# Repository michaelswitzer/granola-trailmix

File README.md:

# TrailMix by Granola Arcade

The TrailMix is a button box style arcade controller by Granola Arcade. It is designed to provide the minimum cost professional grade arcade stick available. The design of the TrailMix is simplified down to the core, without any of the bells and whistles that add cost and complexity. Win your local without breaking the bank!

You can no longer buy the TrailMix from Granola but you can buy our current controllers at https://granola.games

## Should you make a TrailMix?
Building your own TrailMix will definitely be more expensive than buying one directly from Granola Arcade, and it isn't as fun to put together as some of the other DIY options out there. Nevertheless, if you decide to press on, the files in this repository should have everything you need.

## How to build
To build your own TrailMix, import the PCB designs and bill of materials using KiCAD. I provided a list of parts that use JLCPCB's part assembly services, since that is the company I use to manufacture the PCB. You can use these files as a starting point for building your own PCB.

The STL file for the case is optimized for FDM 3D printers. I recommend PLA with at least 15% infill but you can use any material you wish. The case is designed to be printed on the thin edge on the top side, which can cause some stability challenges when printing. **This orientation is better suited to printers that do not move their print bed side to side, and can be tricky to print on Prusa/Ender/etc. printers.** If you use a "bed slinger" printer such as these, make sure you have good bed adhesion.

You will also need to source your own key switches and keycaps. The TrailMix uses Kailh low-profile "Choc v1" keyboard switches.

## Firmware
The TrailMix is designed to use the <a rel="GP2040-CE firmware" href="https://github.com/OpenStickCommunity/GP2040-CE">GP2040-CE firmware</a>. You want the .uf2 file for the Raspberry Pi Pico as it has the same pinouts as the TrailMix. If you wish to use different firmware, you can view the schematic files to understand the layout of the board. If you bridge the Boot and GND pins (marked "BOOT" on the PCB) as you plug in the USB cord, you can upload new firmware in .uf2 format.

## Credits
The TrailMix was designed by Michael Switzer. The GP2040-CE firmware is maintained by <a href="https://github.com/OpenStickCommunity">OpenStickCommunity</a>. This project was inspired by the <a href="https://github.com/jfedor2/flatbox">Flatbox</a>.

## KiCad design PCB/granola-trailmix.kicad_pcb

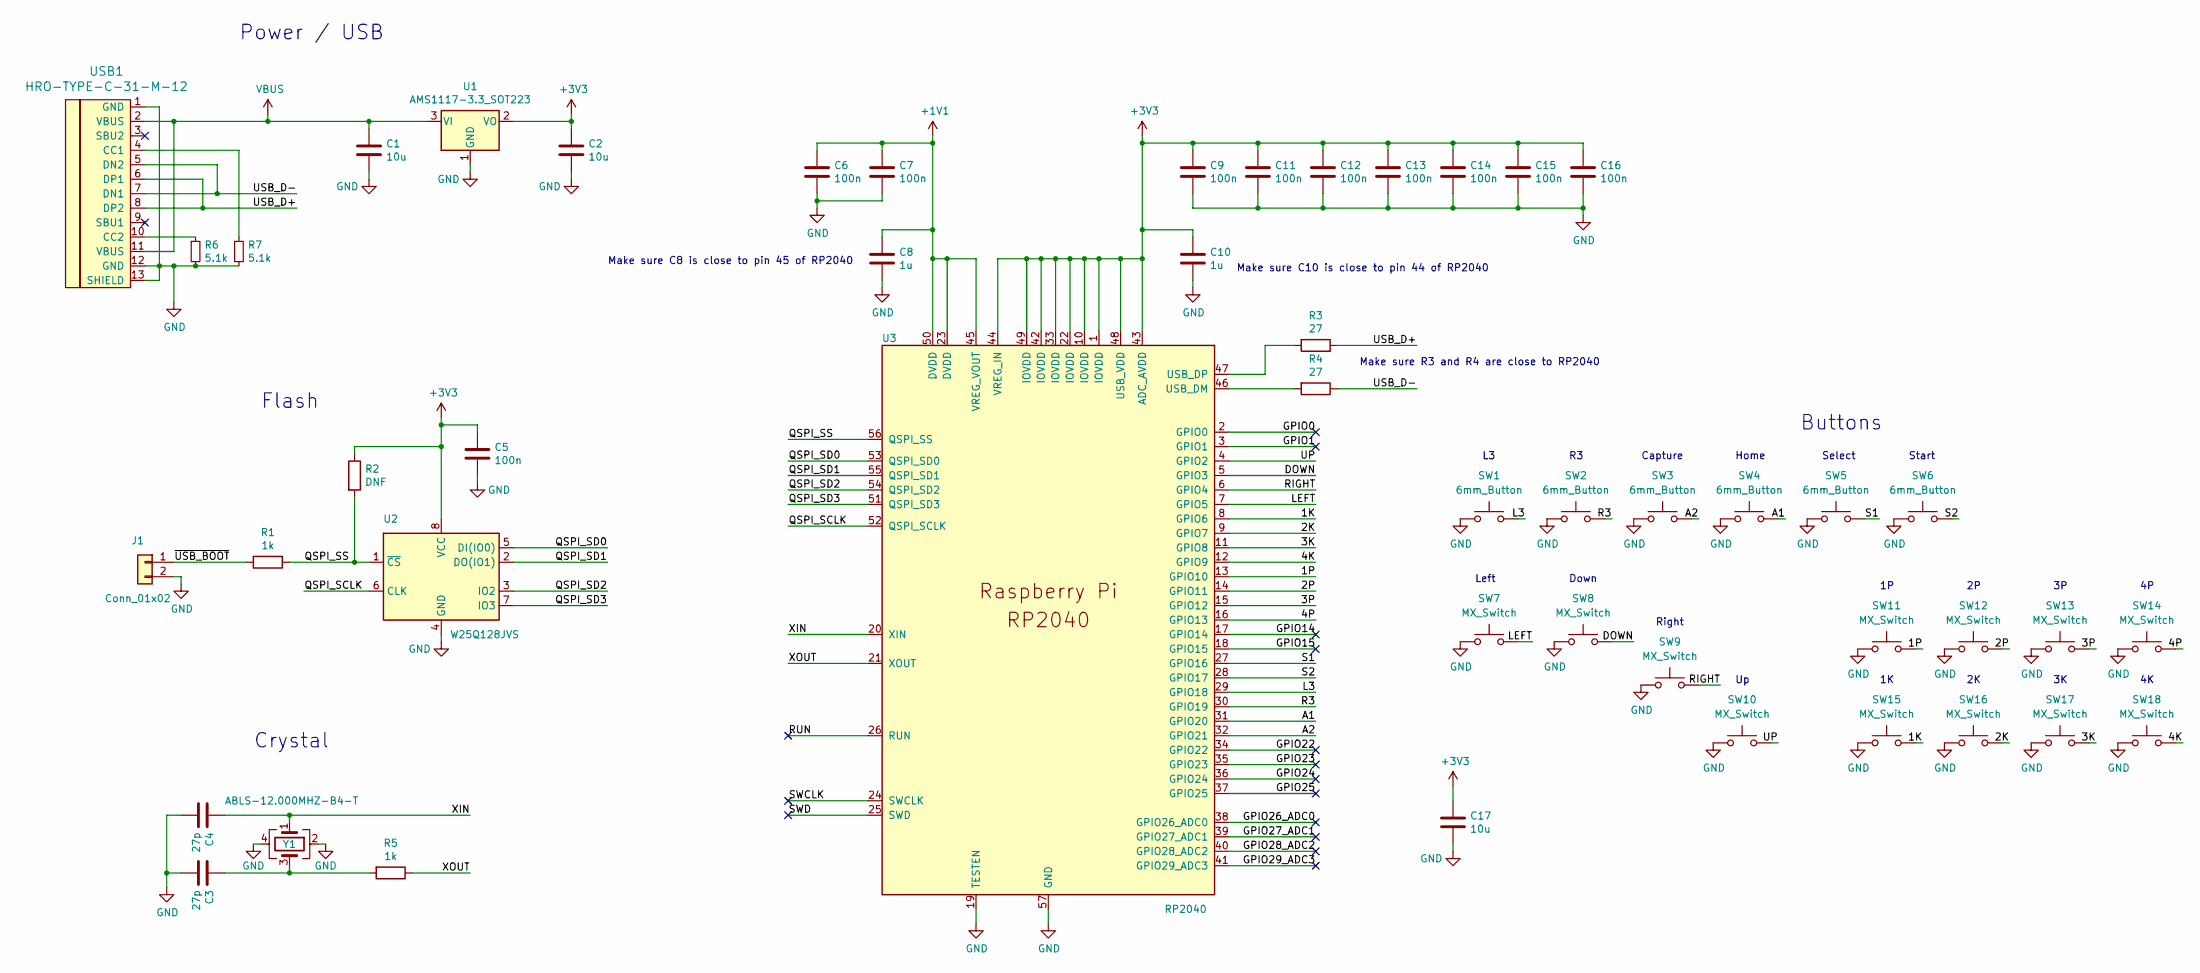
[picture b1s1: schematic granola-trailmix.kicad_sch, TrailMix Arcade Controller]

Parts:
C1, C2, C17: 10u; C_0805_2012Metric; LCSC C83061
C3, C4: 27p; C_0402_1005Metric; LCSC C147436
C5, C6, C7, C9, C11, C12, C13, C14, C15, C16: 100n; C_0402_1005Metric; LCSC C115671
C8, C10: 1u; C_0402_1005Metric; LCSC C5137485
J1: Conn_01x02; PinHeader_1x02_P2.54mm_Vertical
R1, R5: 1k; C_0402_1005Metric; LCSC C105637
R2: DNF; C_0402_1005Metric
R3, R4: 27; C_0402_1005Metric; LCSC C2909343
R6, R7: 5.1k; R_0402_1005Metric; LCSC C25905
SW1, SW2, SW3, SW4, SW5, SW6: 6mm_Button; SW_PUSH_6mm; LCSC C782807
SW7, SW8, SW9, SW10, SW11, SW12, SW13, SW14, SW15, SW16, SW17, SW18: MX_Switch; SW_Kailh_Choc_V1_1.00u
U1: AMS1117-3.3_SOT223; SOT-223-3_TabPin2; LCSC C5250992
U2: W25Q128JVS; SOIC-8_5.23x5.23mm_P1.27mm; LCSC C97521
U3: RP2040; RP2040-QFN-56; LCSC C2040
USB1: HRO-TYPE-C-31-M-12; HRO-TYPE-C-31-M-12-Assembly; LCSC C165948
Y1: ABLS-12.000MHZ-B4-T; Crystal_SMD_3225-4Pin_3.2x2.5mm; LCSC C9002

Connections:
+1V1: C6.1, C7.1, C8.1, U3.23 (DVDD), U3.45 (VREG_VOUT), U3.50 (DVDD)
+3V3: C2.1, C5.1, C9.1, C10.1, C11.1, C12.1, C13.1, C14.1, C15.1, C16.1, C17.1, R2.1, U1.2 (VO), U2.8 (VCC), U3.1 (IOVDD), U3.10 (IOVDD), U3.22 (IOVDD), U3.33 (IOVDD), U3.42 (IOVDD), U3.43 (ADC_AVDD), U3.44 (VREG_IN), U3.48 (USB_VDD), U3.49 (IOVDD)
/1K: SW15.1 (A), U3.8 (GPIO6)
/1P: SW11.1 (A), U3.13 (GPIO10)
/2K: SW16.1 (A), U3.9 (GPIO7)
/2P: SW12.1 (A), U3.14 (GPIO11)
/3K: SW17.1 (A), U3.11 (GPIO8)
/3P: SW13.1 (A), U3.15 (GPIO12)
/4K: SW18.1 (A), U3.12 (GPIO9)
/4P: SW14.1 (A), U3.16 (GPIO13)
/A1: SW4.1 (A), U3.31 (GPIO20)
/A2: SW3.1 (A), U3.32 (GPIO21)
/DOWN: SW8.1 (A), U3.5 (GPIO3)
/GPIO0: U3.2 (GPIO0)
/GPIO1: U3.3 (GPIO1)
/GPIO14: U3.17 (GPIO14)
/GPIO15: U3.18 (GPIO15)
/GPIO22: U3.34 (GPIO22)
/GPIO23: U3.35 (GPIO23)
/GPIO24: U3.36 (GPIO24)
/GPIO25: U3.37 (GPIO25)
/GPIO26_ADC0: U3.38 (GPIO26_ADC0)
/GPIO27_ADC1: U3.39 (GPIO27_ADC1)
/GPIO28_ADC2: U3.40 (GPIO28_ADC2)
/GPIO29_ADC3: U3.41 (GPIO29_ADC3)
/L3: SW1.1 (A), U3.29 (GPIO18)
/LEFT: SW7.1 (A), U3.7 (GPIO5)
/QSPI_SCLK: U2.6 (CLK), U3.52 (QSPI_SCLK)
/QSPI_SD0: U2.5 (DI(IO0)), U3.53 (QSPI_SD0)
/QSPI_SD1: U2.2 (DO(IO1)), U3.55 (QSPI_SD1)
/QSPI_SD2: U2.3 (IO2), U3.54 (QSPI_SD2)
/QSPI_SD3: U2.7 (IO3), U3.51 (QSPI_SD3)
/QSPI_SS: R1.1, R2.2, U2.1 (~CS), U3.56 (QSPI_SS)
/R3: SW2.1 (A), U3.30 (GPIO19)
/RIGHT: SW9.1 (A), U3.6 (GPIO4)
/RUN: U3.26 (RUN)
/S1: SW5.1 (A), U3.27 (GPIO16)
/S2: SW6.1 (A), U3.28 (GPIO17)
/SWCLK: U3.24 (SWCLK)
/SWD: U3.25 (SWD)
/UP: SW10.1 (A), U3.4 (GPIO2)
/USB_D+: R3.1, USB1.6 (DP1), USB1.8 (DP2)
/USB_D-: R4.1, USB1.5 (DN2), USB1.7 (DN1)
/XIN: C4.1, U3.20 (XIN), Y1.1
/XOUT: R5.1, U3.21 (XOUT)
/~USB_BOOT: J1.1, R1.2
GND: C1.2, C2.2, C3.2, C4.2, C5.2, C6.2, C7.2, C8.2, C9.2, C10.2, C11.2, C12.2, C13.2, C14.2, C15.2, C16.2, C17.2, J1.2, R6.2, R7.2, SW1.2 (B), SW2.2 (B), SW3.2 (B), SW4.2 (B), SW5.2 (B), SW6.2 (B), SW7.2 (B), SW8.2 (B), SW9.2 (B), SW10.2 (B), SW11.2 (B), SW12.2 (B), SW13.2 (B), SW14.2 (B), SW15.2 (B), SW16.2 (B), SW17.2 (B), SW18.2 (B), U1.1 (GND), U2.4 (GND), U3.19 (TESTEN), U3.57 (GND), USB1.1 (GND), USB1.12 (GND), USB1.13 (SHIELD), Y1.2, Y1.4
unnamed: C3.1, R5.2, Y1.3
unnamed: R3.2, U3.47 (USB_DP)
unnamed: R4.2, U3.46 (USB_DM)
unnamed: R6.1, USB1.10 (CC2)
unnamed: R7.1, USB1.4 (CC1)
VBUS: C1.1, U1.3 (VI), USB1.2 (VBUS), USB1.11 (VBUS)

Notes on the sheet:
Right
Start
Capture
Down
Left
Make sure R3 and R4 are close to RP2040
Crystal
Make sure C10 is close to pin 44 of RP2040
Flash
Power / USB
Select
Buttons
Home
Make sure C8 is close to pin 45 of RP2040

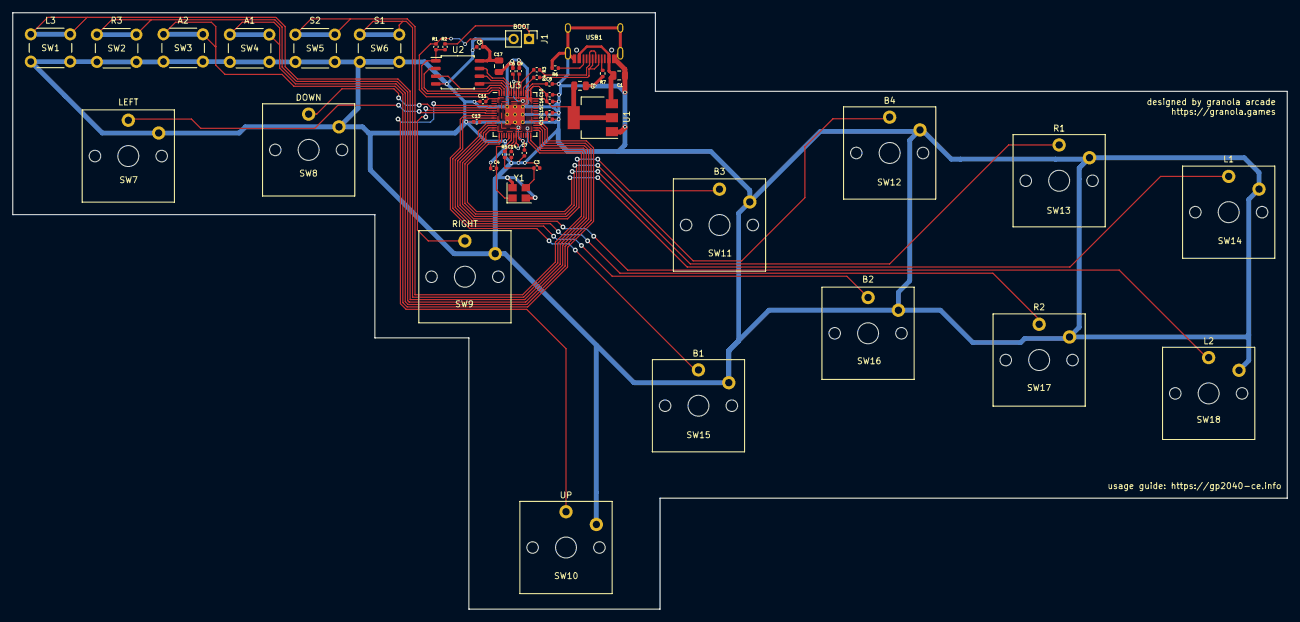
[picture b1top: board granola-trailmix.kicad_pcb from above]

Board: 2 copper layers, 210.1 x 98.3 mm, 48 parts (0 on the bottom side), 38 nets.

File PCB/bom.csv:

Comment,Designator,Footprint,LCSC Part Number
10uF,"C1,C2",Capacitor_SMD:C_0805_2012Metric,C83061
27p,"C3,C4",Capacitor_SMD:C_0402_1005Metric,C147436
100nF,"C5,C6,C7,C9,C11,C12,C13,C14,C15,C16",Capacitor_SMD:C_0402_1005Metric,C115671
1uF,"C8,C10",Capacitor_SMD:C_0402_1005Metric,C5137485
10uF,C17,Capacitor_SMD:C_0805_2012Metric,C83061
"HRO-TYPE-C-31-M-12","USB1","Type-C:HRO-TYPE-C-31-M-12-Assembly","C165948"
1k,"R1,R5",Capacitor_SMD:C_0402_1005Metric,C105637
"5.1k","R6,R7","Resistor_SMD:R_0402_1005Metric","C25905"
27 ohm,"R3,R4",Capacitor_SMD:C_0402_1005Metric,C2909343
6mm_Button,"SW1,SW2,SW3,SW4,SW5,SW6",Button_Switch_THT:SW_PUSH_6mm,C782807
AMS1117,U1,Package_TO_SOT_SMD:SOT-223-3_TabPin2,C5250992
W25Q128JVS,U2,Package_SO:SOIC-8_5.23x5.23mm_P1.27mm,C97521
RP2040,U3,RP2040_minimal:RP2040-QFN-56,C2040
12MHZ,Y1,RP2040_minimal:Crystal_SMD_HC49-US,C390753

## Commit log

2023-05-26 Design files
2023-05-26 readme update
2023-05-26 bill of materials
2023-05-27 cleanup, gitignore
2023-06-03 usb-c
2023-06-03 gerber files
2023-07-04 vertical print case, minor pcb changes
2023-07-04 case print orientation
2023-07-06 readme image
2023-07-06 readme headers update
2023-07-07 removed easter egg as it doesn't show up on an actually nice printer
2023-07-11 small case dimension adjustment for more reliable fit
2023-07-11 moved logo to avoid impact with buttons
2023-07-12 Just a bit more adjustments
2023-07-13 Slightly widen case to accomodate PCB tolerances
2023-07-20 remove chamfer to make warping less likely
2023-07-28 Updated PCB to new crystal. Added version of TrailMix case that has no front design.
2023-08-02 added non slip pads for case
2023-09-15 case model switch to step files from stl
2024-04-06 Updated case design
2024-04-06 Create LICENSE
